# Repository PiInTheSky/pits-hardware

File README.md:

Hardware for the Pi In The Sky Project.

These files are done in Cadsoft Eagle 6.4

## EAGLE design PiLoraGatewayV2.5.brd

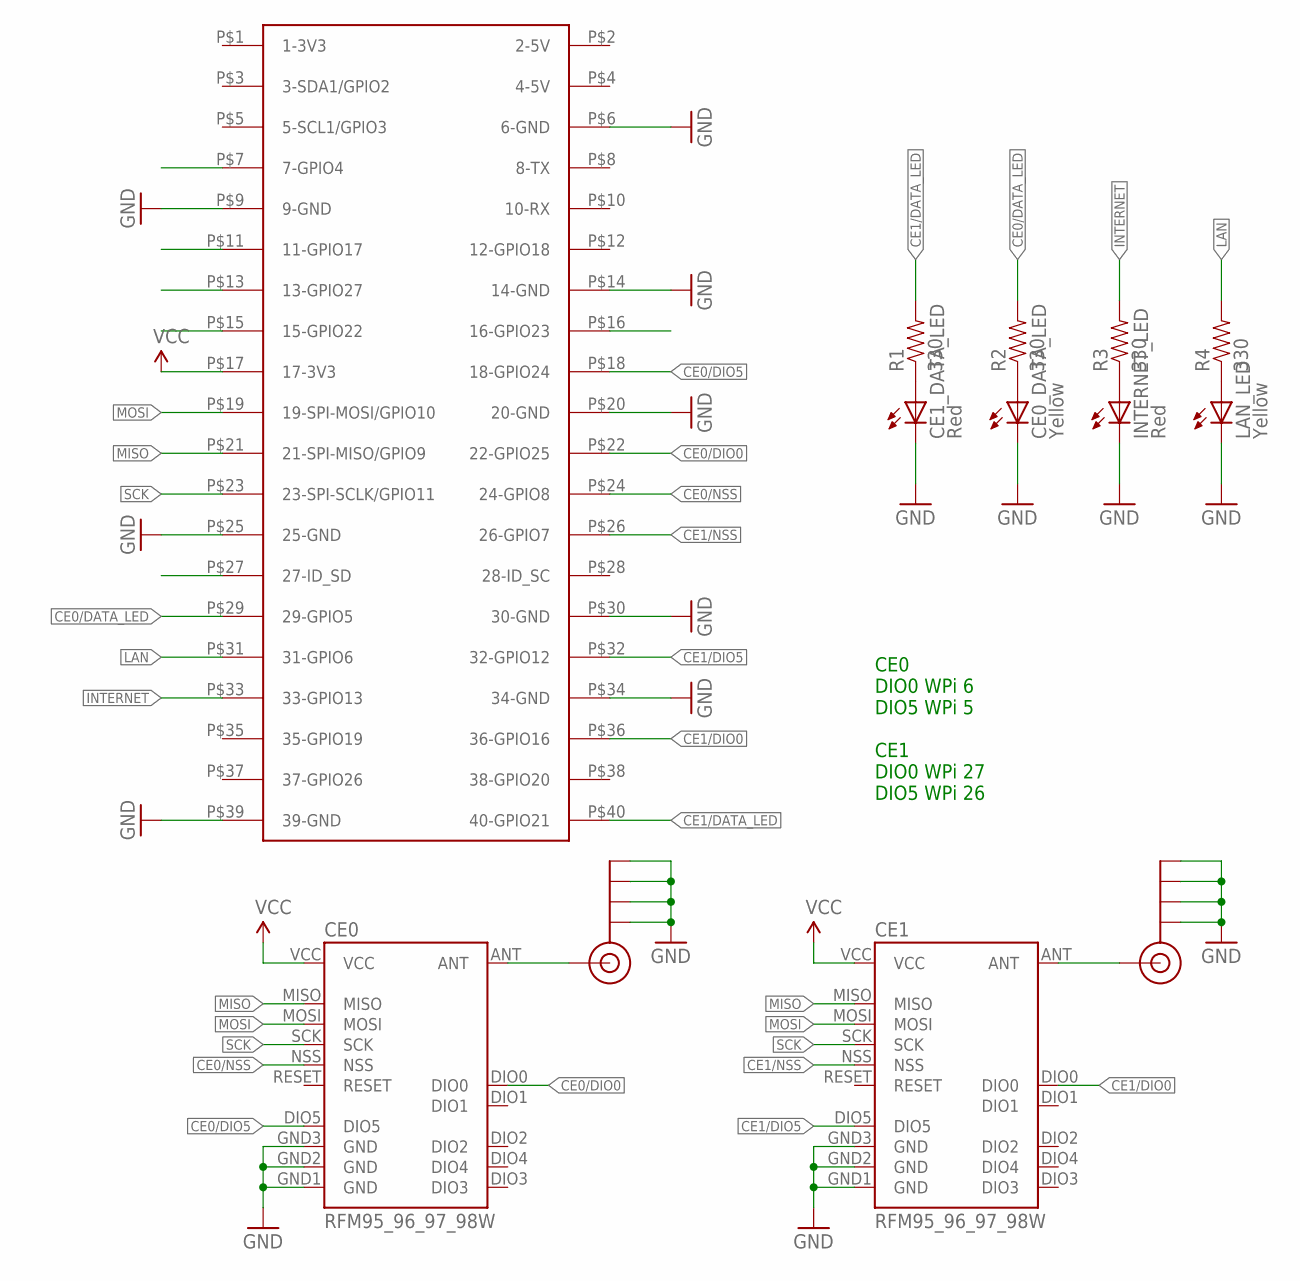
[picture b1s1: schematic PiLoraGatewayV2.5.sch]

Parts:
CE0, CE1: RFM95_96_97_98W
CE0_DATA_LED: Yellow; LED-0603
CE1_DATA_LED: Red; LED-0603
INTERNET_LED: Red; LED-0603
J$0, J$1: SMA_EDGE; SMA-EDGE
LAN_LED: Yellow; LED-0603
R1, R2, R3, R4: 330; 0603-RES
U$1: RASPBERRY-PI+; RASPBERRY-PI-PLUS-CAM_NOTCH

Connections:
CE0/DATA_LED: R2.2, U$1.P$29 (29-GPIO5)
CE0/DIO0: CE0.DIO0, U$1.P$22 (22-GPIO25)
CE0/DIO5: CE0.DIO5, U$1.P$18 (18-GPIO24)
CE0/NSS: CE0.NSS, U$1.P$24 (24-GPIO8)
CE1/DATA_LED: R1.2, U$1.P$40 (40-GPIO21)
CE1/DIO0: CE1.DIO0, U$1.P$36 (36-GPIO16)
CE1/DIO5: CE1.DIO5, U$1.P$32 (32-GPIO12)
CE1/NSS: CE1.NSS, U$1.P$26 (26-GPIO7)
GND: CE0.GND1 (GND), CE0.GND2 (GND), CE0.GND3 (GND), CE0_DATA_LED.C, CE1.GND1 (GND), CE1.GND2 (GND), CE1.GND3 (GND), CE1_DATA_LED.C, J$0.GND@0 (GND), J$0.GND@1 (GND), J$0.GND@2 (GND), J$0.GND@3 (GND), J$1.GND@0 (GND), J$1.GND@1 (GND), J$1.GND@2 (GND), J$1.GND@3 (GND), LAN_LED.C, U$1.P$6 (6-GND), U$1.P$9 (9-GND), U$1.P$14 (14-GND), U$1.P$20 (20-GND), U$1.P$25 (25-GND), U$1.P$30 (30-GND), U$1.P$34 (34-GND), U$1.P$39 (39-GND)
INTERNET: R3.2, U$1.P$33 (33-GPIO13)
INTERNET_LED: INTERNET_LED.C
LAN: R4.2, U$1.P$31 (31-GPIO6)
MISO: CE0.MISO, CE1.MISO, U$1.P$21 (21-SPI-MISO/GPIO9)
MOSI: CE0.MOSI, CE1.MOSI, U$1.P$19 (19-SPI-MOSI/GPIO10)
unnamed: CE0.ANT, J$0.SIG (SIGNAL)
unnamed: CE1.ANT, J$1.SIG (SIGNAL)
unnamed: INTERNET_LED.A, R3.1
unnamed: LAN_LED.A, R4.1
unnamed: CE0_DATA_LED.A, R2.1
unnamed: CE1_DATA_LED.A, R1.1
SCK: CE0.SCK, CE1.SCK, U$1.P$23 (23-SPI-SCLK/GPIO11)
VCC: CE0.VCC, CE1.VCC, U$1.P$17 (17-3V3)

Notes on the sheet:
CE0 DIO0 WPi 6 DIO5 WPi 5 CE1 DIO0 WPi 27 DIO5 WPi 26

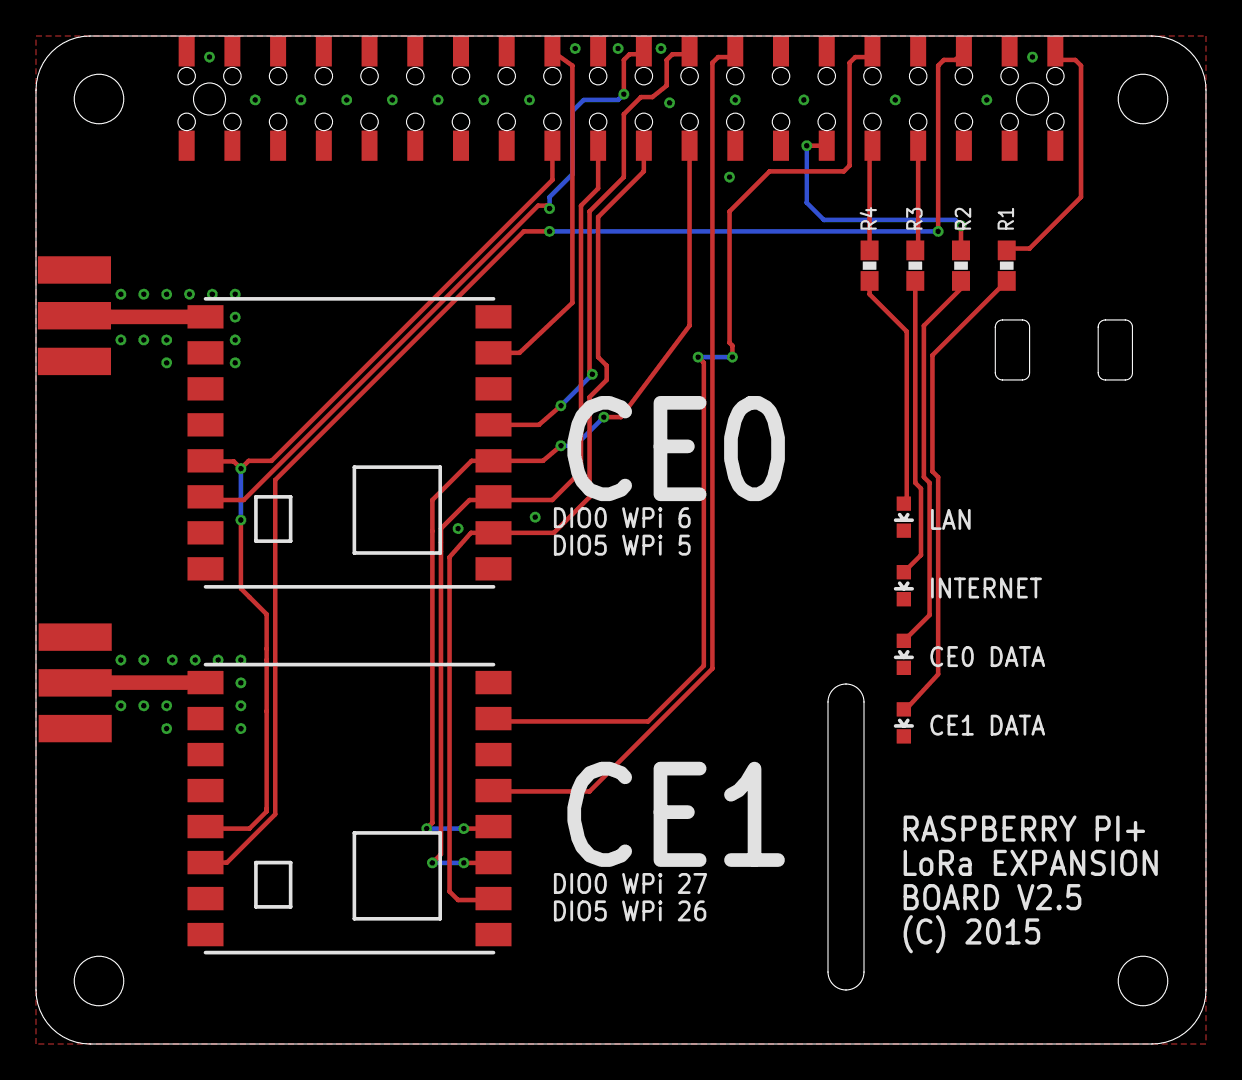
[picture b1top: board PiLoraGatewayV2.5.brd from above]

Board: 2 copper layers, 65.0 x 56.0 mm, 13 parts (0 on the bottom side), 21 nets.

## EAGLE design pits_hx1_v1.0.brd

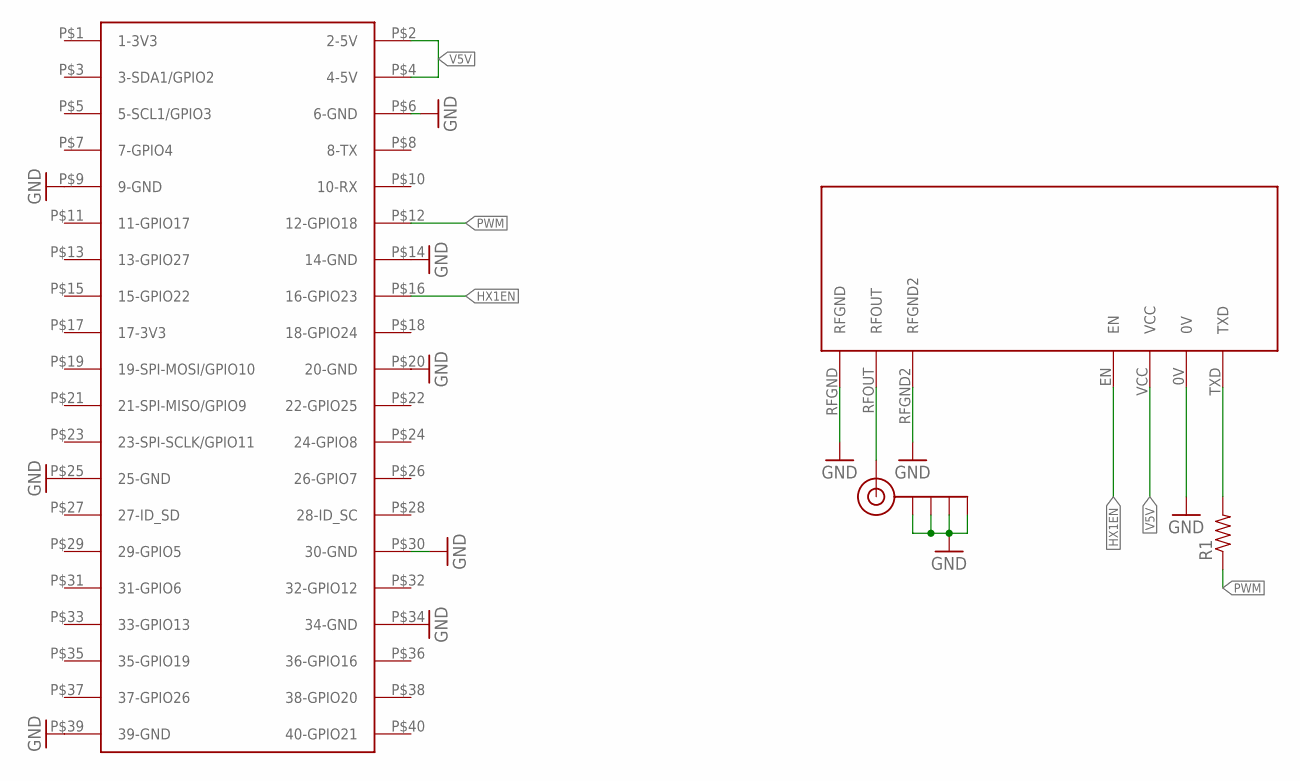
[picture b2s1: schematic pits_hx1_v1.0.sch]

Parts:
J$1: SMA_EDGE; SMA-EDGE
R1: RESISTOR0603-RES; 0603-RES
U$1: RASPBERRY-PI+; RASPBERRY-PI-PLUS-CAM_NOTCH
U$2: RADIOMETRIX-HX1

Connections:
GND: J$1.GND@0 (GND), J$1.GND@1 (GND), J$1.GND@2 (GND), J$1.GND@3 (GND), U$1.P$6 (6-GND), U$1.P$9 (9-GND), U$1.P$14 (14-GND), U$1.P$20 (20-GND), U$1.P$25 (25-GND), U$1.P$30 (30-GND), U$1.P$34 (34-GND), U$1.P$39 (39-GND), U$2.0V, U$2.RFGND, U$2.RFGND2
HX1EN: U$1.P$16 (16-GPIO23), U$2.EN
unnamed: R1.2, U$2.TXD
unnamed: J$1.SIG (SIGNAL), U$2.RFOUT
PWM: R1.1, U$1.P$12 (12-GPIO18)
V5V: U$1.P$2 (2-5V), U$1.P$4 (4-5V), U$2.VCC

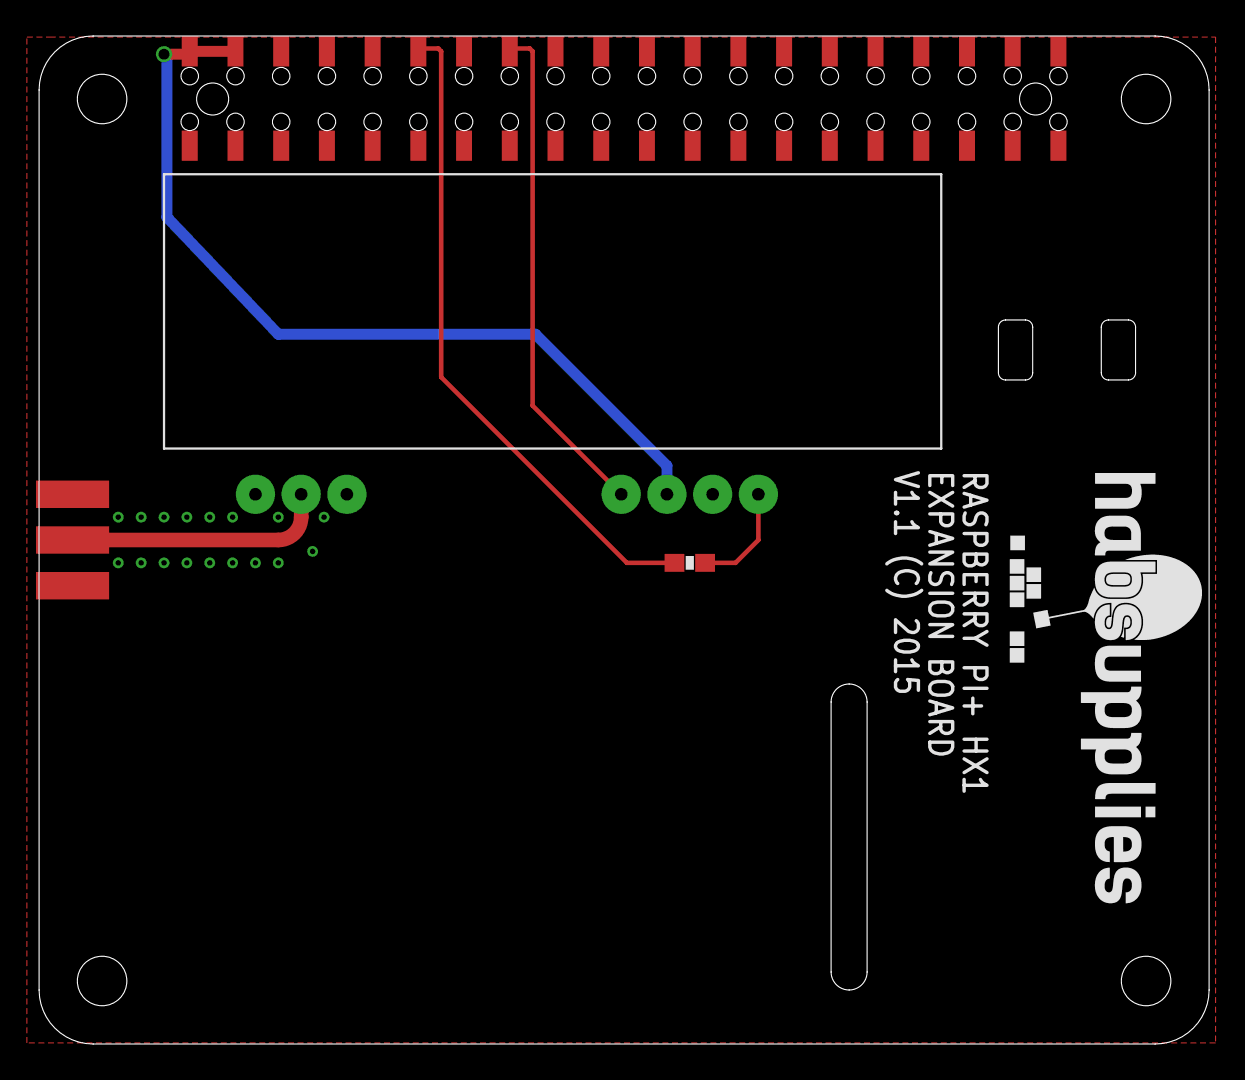
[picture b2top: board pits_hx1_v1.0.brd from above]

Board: 2 copper layers, 65.0 x 56.0 mm, 5 parts (0 on the bottom side), 6 nets.

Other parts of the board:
U$3: NEW-HS-LOGO-MED

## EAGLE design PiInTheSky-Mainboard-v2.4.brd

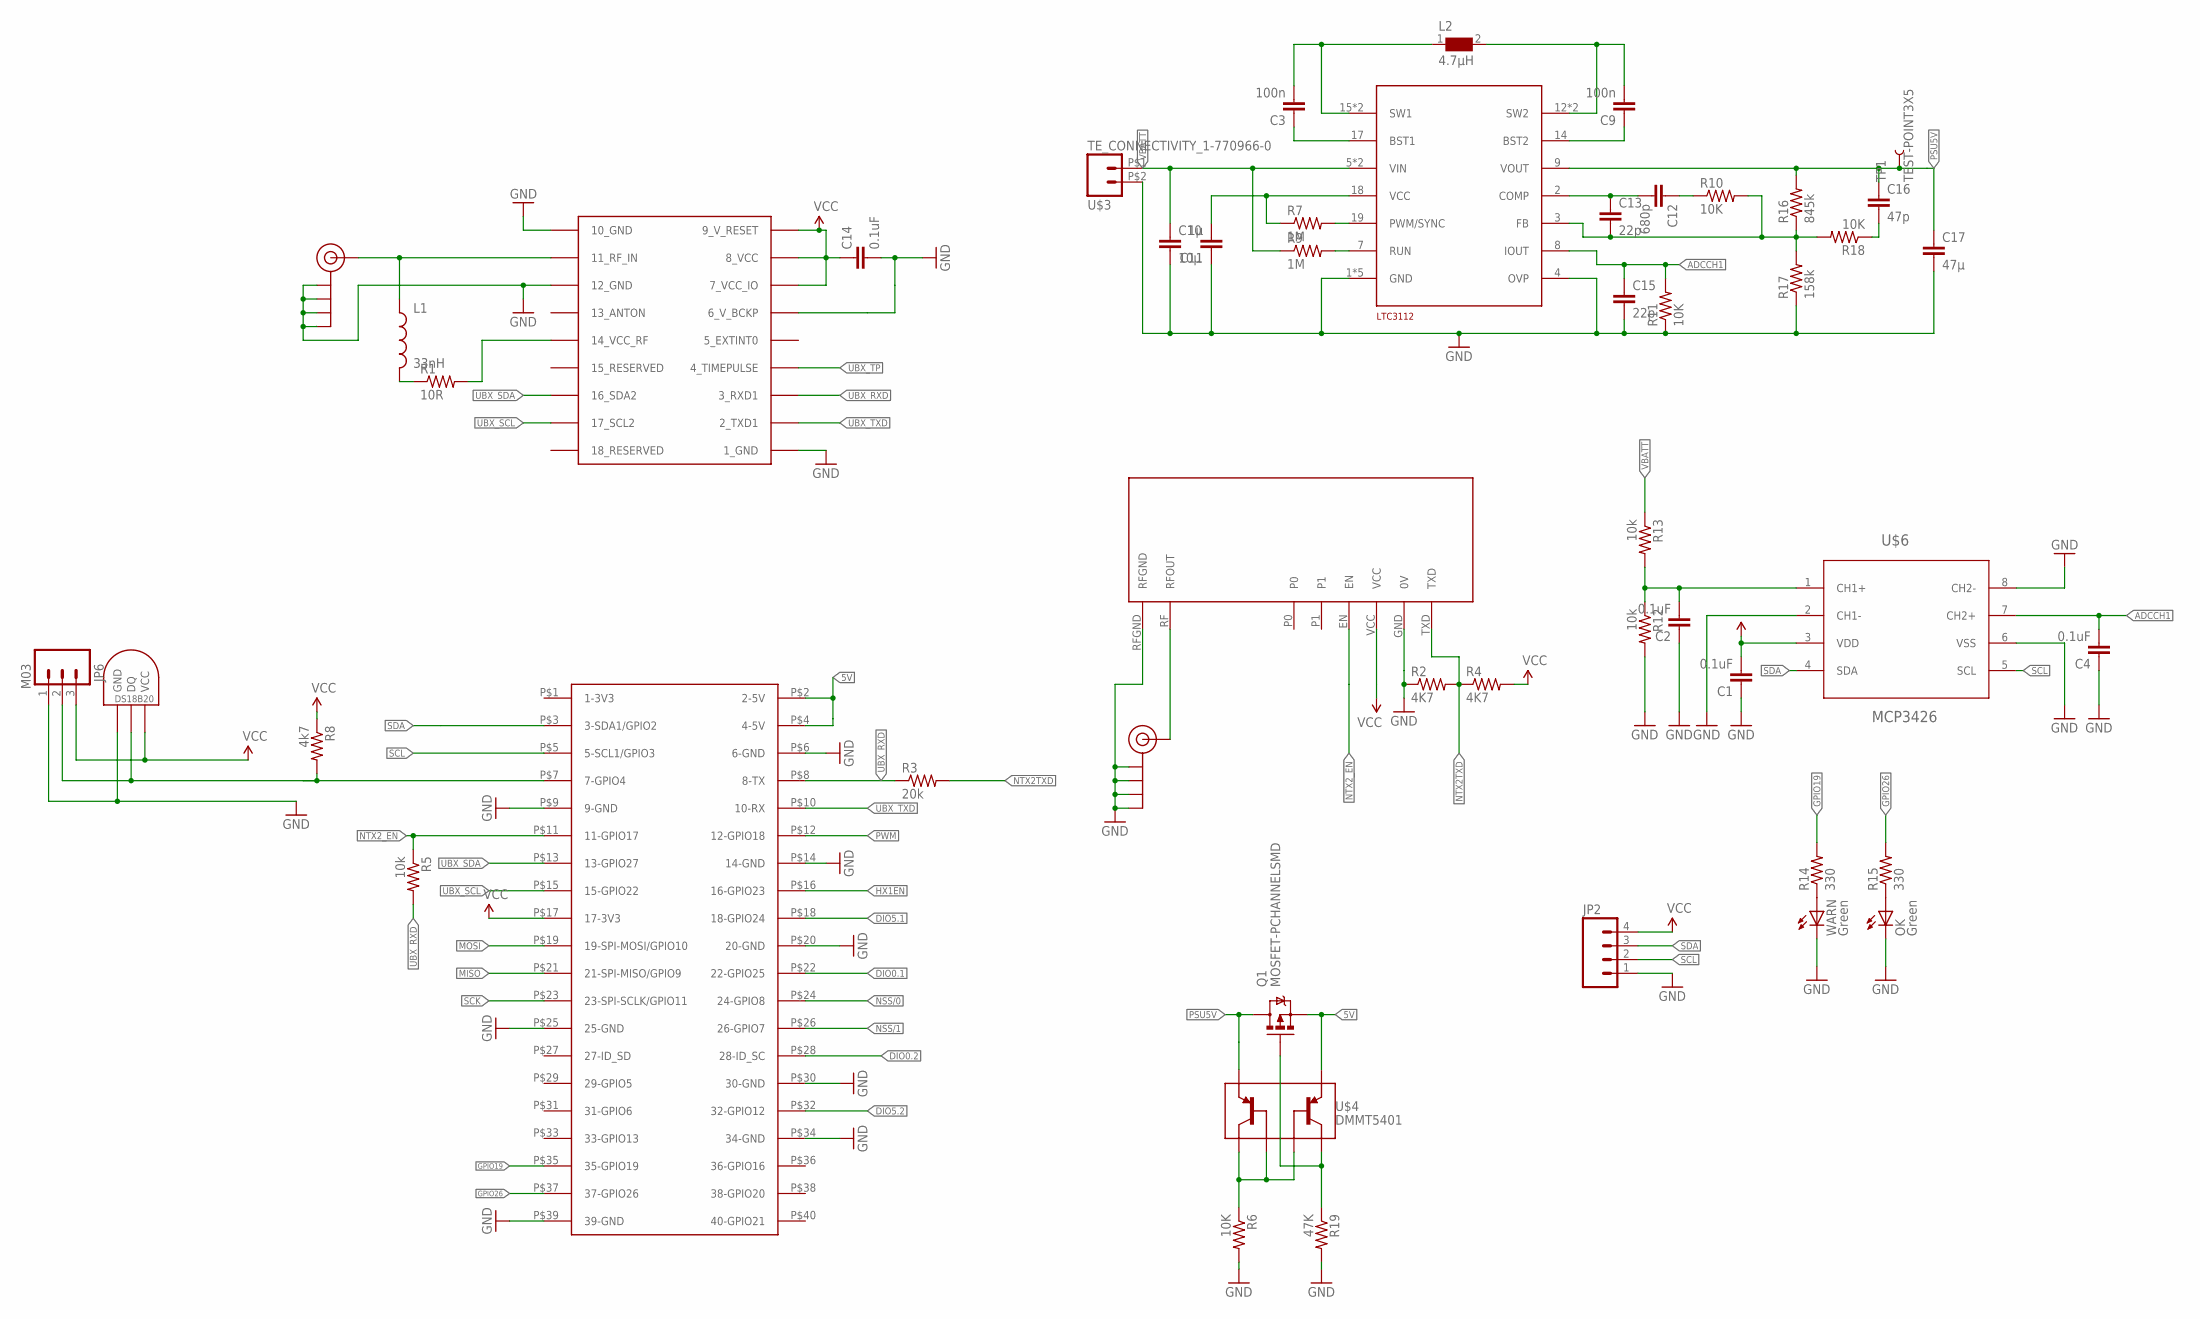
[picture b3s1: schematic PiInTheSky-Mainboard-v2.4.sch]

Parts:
C1, C2, C4, C14: 0.1uF; 0603-CAP
C3, C9: 100n; 0603-CAP
C10: 10µ; 1206
C11: 1µ; 0603-CAP
C12: 680p; 0603-CAP
C13, C15: 22p; 0603-CAP
C16: 47p; 0603-CAP
C17: 47µ; 1206
J$1, J$2: SMA_EDGE; SMA-EDGE
JP2: M04PTH; 1X04
JP6: M03; M03-JST
L1: 33nH; 0603
L2: 4.7µH; WE-HCI_7030/7040/7050
OK: Green; LED-0603
Q1: MOSFET-PCHANNELSMD; SOT23-3
R1: 10R; 0603-RES
R2, R4: 4K7; 0603-RES
R3: 20k; 0603-RES
R5, R12, R13: 10k; 0603-RES
R6, R10, R11, R18: 10K; 0603-RES
R7, R9: 1M; 0603-RES
R8: 4k7; 0603-RES
R14, R15: 330; 0603-RES
R16: 845k; 0603-RES
R17: 158k; 0603-RES
R19: 47K; 0603-RES
TEMP: DS1821; DS18B20_SOIC
TP1: TEST-POINT3X5; PAD.03X.05
U$1: RASPBERRY-PI+; RASPBERRY-PI-PLUS-CAM_NOTCH
U$3: TE_CONNECTIVITY_1-770966-0; FARNELL 1098556
U$4: DMMT5401; SOT26
U$5: LTC3112; TSSOP-20
U$6: MCP3426; SOIC127P600X175-8N
U$7: UBLOX_MAX
U$8: RADIOMETRIX-MTX2
WARN: Green; LED-0603

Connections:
5V: Q1.2 (S), U$1.P$2 (2-5V), U$1.P$4 (4-5V), U$4.5 (E2)
ADCCH1: C4.2, C15.1, R11.2, U$5.8 (IOUT), U$6.7 (CH2+)
DIO0.1: U$1.P$22 (22-GPIO25)
DIO0.2: U$1.P$28 (28-ID_SC)
DIO5.1: U$1.P$18 (18-GPIO24)
DIO5.2: U$1.P$32 (32-GPIO12)
GND: C1.1, C2.1, C4.1, C10.2, C11.1, C14.2, C15.2, C17.2, J$1.GND@0 (GND), J$1.GND@1 (GND), J$1.GND@2 (GND), J$1.GND@3 (GND), J$2.GND@0 (GND), J$2.GND@1 (GND), J$2.GND@2 (GND), J$2.GND@3 (GND), JP2.1, JP6.1, OK.C, R2.1, R6.2, R11.1, R12.2, R17.1, R19.2, TEMP.GND, U$1.P$6 (6-GND), U$1.P$9 (9-GND), U$1.P$14 (14-GND), U$1.P$20 (20-GND), U$1.P$25 (25-GND), U$1.P$30 (30-GND), U$1.P$34 (34-GND), U$1.P$39 (39-GND), U$3.P$2 (2), U$5.1 (GND), U$5.4 (OVP), U$5.10 (GND), U$5.11 (GND), U$5.20 (GND), U$5.21 (GND), U$6.2 (CH1-), U$6.6 (VSS), U$6.8 (CH2-), U$7.1_GND, U$7.6_V_BCKP, U$7.10_GND, U$7.12_GND, U$8.GND (0V), U$8.RFGND, WARN.C
GPIO1: JP6.2, R8.2, TEMP.DQ, U$1.P$7 (7-GPIO4)
GPIO19: R14.2, U$1.P$35 (35-GPIO19)
GPIO26: R15.2, U$1.P$37 (37-GPIO26)
HX1EN: U$1.P$16 (16-GPIO23)
MISO: U$1.P$21 (21-SPI-MISO/GPIO9)
MOSI: U$1.P$19 (19-SPI-MOSI/GPIO10)
unnamed: J$1.SIG (SIGNAL), L1.1, U$7.11_RF_IN
unnamed: R1.2, U$7.14_VCC_RF
unnamed: L1.2, R1.1
unnamed: J$2.SIG (SIGNAL), U$8.RF (RFOUT)
unnamed: C3.1, U$5.17 (BST1)
unnamed: C2.2, R12.1, R13.2, U$6.1 (CH1+)
unnamed: R6.1, U$4.1 (C1), U$4.2 (B1), U$4.3 (B2)
unnamed: C9.1, U$5.14 (BST2)
unnamed: C9.2, L2.2, U$5.12 (SW2), U$5.13 (SW2)
unnamed: OK.A, R15.1
unnamed: C3.2, L2.1, U$5.15 (SW1), U$5.16 (SW1)
unnamed: C11.2, R7.1, U$5.18 (VCC)
unnamed: R9.2, U$5.7 (RUN)
unnamed: R14.1, WARN.A
unnamed: R7.2, U$5.19 (PWM/SYNC)
unnamed: C13.2, R10.2, R16.1, R17.2, R18.2, U$5.3 (FB)
unnamed: C12.2, C13.1, U$5.2 (COMP)
unnamed: C12.1, R10.1
unnamed: C16.2, R18.1
unnamed: Q1.1 (G), R19.1, U$4.4 (C2)
NSS/0: U$1.P$24 (24-GPIO8)
NSS/1: U$1.P$26 (26-GPIO7)
NTX2TXD: R2.2, R3.2, R4.1, U$8.TXD
NTX2_EN: R5.1, U$1.P$11 (11-GPIO17), U$8.EN
PSU5V: C16.1, C17.1, Q1.3 (D), R16.2, TP1.P$1, U$4.6 (E1), U$5.9 (VOUT)
PWM: U$1.P$12 (12-GPIO18)
SCK: U$1.P$23 (23-SPI-SCLK/GPIO11)
SCL: JP2.2, U$1.P$5 (5-SCL1/GPIO3), U$6.5 (SCL)
SDA: JP2.3, U$1.P$3 (3-SDA1/GPIO2), U$6.4 (SDA)
UBX_RXD: R3.1, R5.2, U$1.P$8 (8-TX), U$7.3_RXD1
UBX_SCL: U$1.P$15 (15-GPIO22), U$7.17_SCL2
UBX_SDA: U$1.P$13 (13-GPIO27), U$7.16_SDA2
UBX_TP: U$7.4_TIMEPULSE
UBX_TXD: U$1.P$10 (10-RX), U$7.2_TXD1
VBATT: C10.1, R9.1, R13.1, U$3.P$1 (1), U$5.5 (VIN), U$5.6 (VIN)
VCC: C1.2, C14.1, JP2.4, JP6.3, R4.2, R8.1, TEMP.VCC, U$1.P$17 (17-3V3), U$6.3 (VDD), U$7.7_VCC_IO, U$7.8_VCC, U$7.9_V_RESET, U$8.VCC

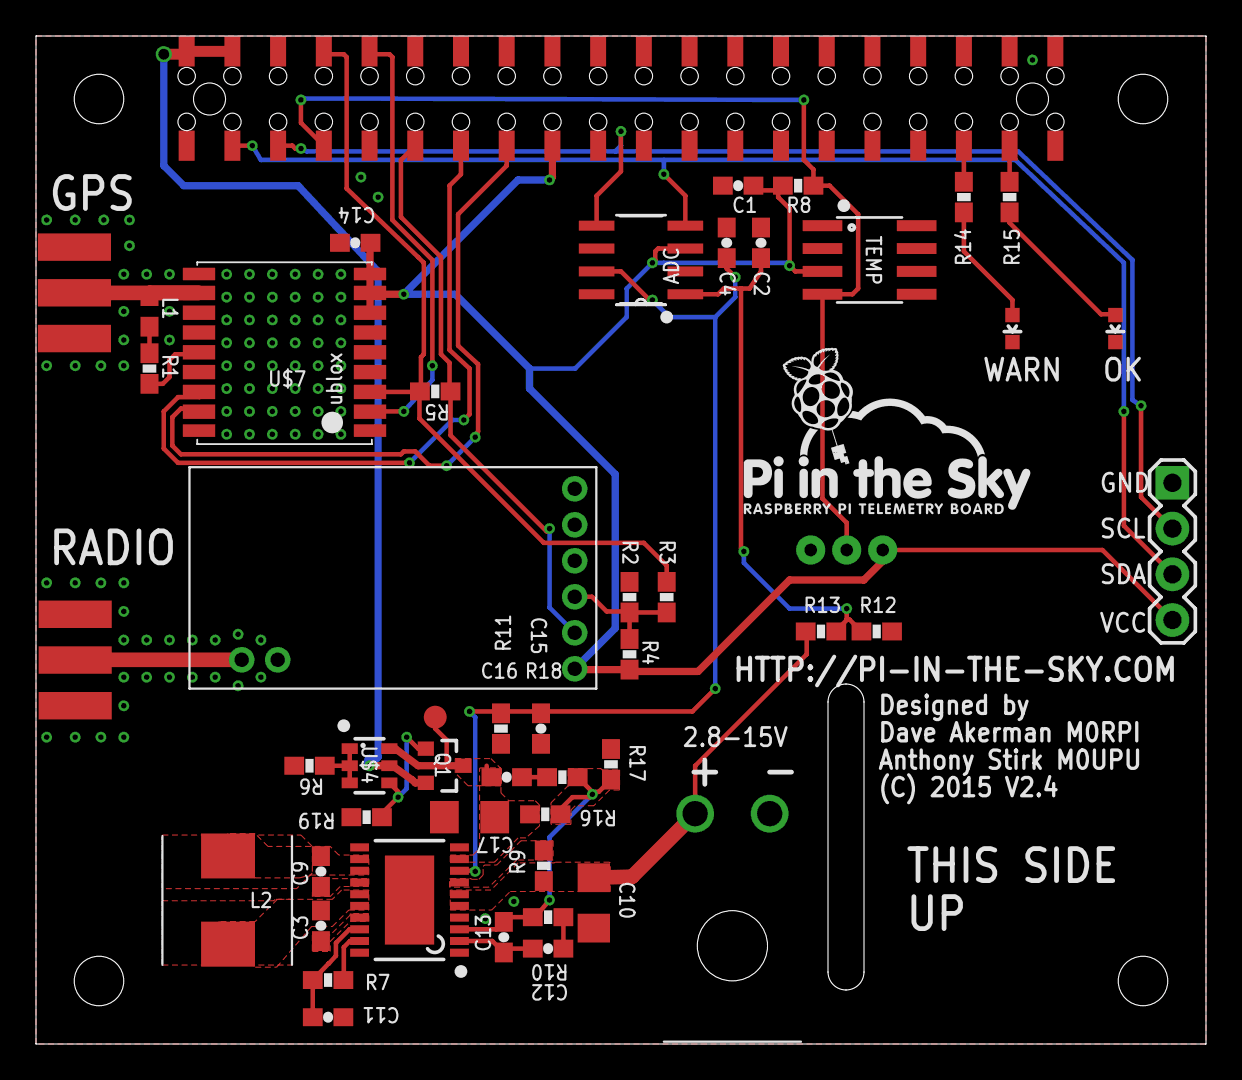
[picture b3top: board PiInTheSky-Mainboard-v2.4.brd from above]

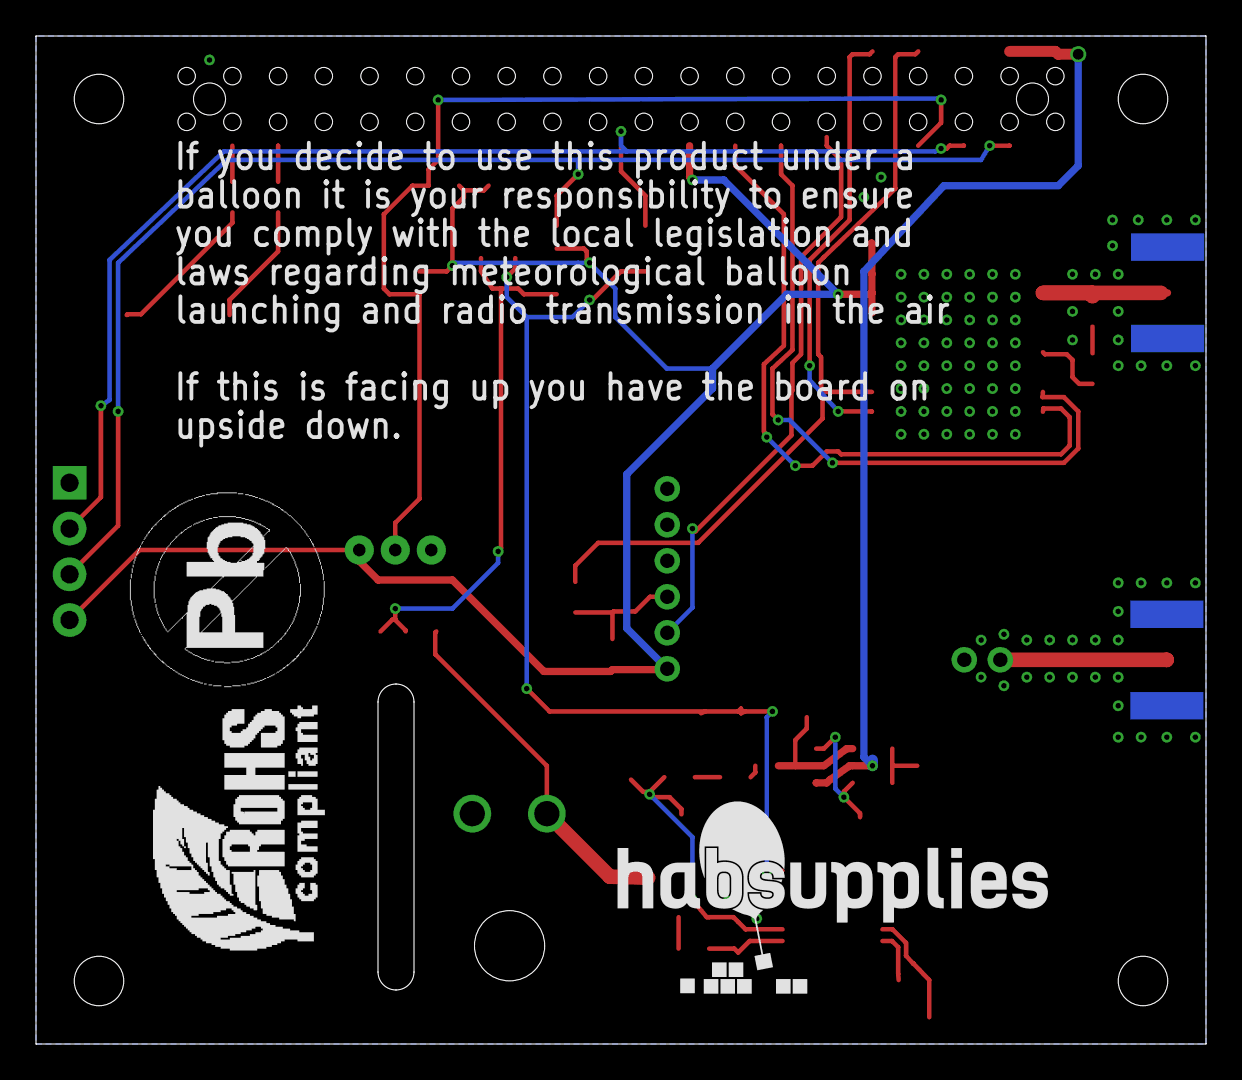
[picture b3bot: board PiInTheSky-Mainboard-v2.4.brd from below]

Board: 2 copper layers, 65.0 x 56.0 mm, 54 parts (3 on the bottom side), 37 nets.

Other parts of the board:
E$12: NOPB_LOGO_SYM
E$13: ROHS_LOGO_LEAF_SYM
U$2: PITS_LOGO_SMALL
U$9: NEW-HS-LOGO-MED

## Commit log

2014-10-28 Initial Commit of PCB Files
    Cadsoft Eagle 6.4
2014-11-11 Pushed V2.3
    Amended enable line on ADC
2015-06-17 Updated with V2.4 Design
    Replaced ADC with MCP3426
2015-06-17 Added Lora Gateway & HX1 Board
2015-07-27 Pits Stacking System GPIO Allocations
    Table of what GPIO's are allocated to what on the PITS Stacking system
2015-07-27 PiLoraGateway V2.4
    Added LED's
2015-08-11 Amended pins for LoRa Board
2015-09-08 Updated GPIO Allocation
    Amended some pins on V2.5 Lora and V2.5 PITS boards
2015-09-08 Correction
2016-04-26 Missing one wire pin
    Whoops.
2016-10-03 Bringing Github repo upto date

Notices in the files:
PiInTheSky-Mainboard-v2.4.brd:
(C) 2015 V2.4
pits_hx1_v1.0.brd:
V1.1 (C) 2015
parts and their libraries:
PatternAgents-Logos: License : http://creativecommons.org/licenses/by-sa/3.0
(Creative Commons 3.0)
SparkFun: Licensing: CC v3.0 Share-Alike You are welcome to use this library for commercial purposes.
